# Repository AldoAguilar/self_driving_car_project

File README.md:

# Self Driving Car Project
This repository is dedicated to the development of a robotic system capable of performing an autonomous driving behavior of a 1/10 RC Vehicle using Control algorithms based in Deep Neural Networks through ROS.

## Table of Contents

* [Project Description](#project-description)
* [Installation](#installation)
  - [Hardware prerequisites](#hardware-prerequisites)
  - [Software prerequisites](#software-prerequisites)
  - [Hardware setup](#hardware-setup)
  - [Software setup](#software-setup)
  - [Network setup](#network-setup)
* [ROS Architecure](#ros-architecture)

## Project Description
The objective of this project is to develop an autonomous driving robotic system using a 1/10 RC Vehicle which is instrumented using specific hardware to control and measure its velocity and direction through ROS. As mentioned, a Deep Neural Network is used to Control the autonomous behavior of the vehicle which is trained and tested using the information of the vehicle's direction and speed data as well as visual and spatial information provided by an RGB/Depth camera and a Lidar sensor mounted in the vehicle.

## Installation
The following steps are aimed to help the user replicate the setting up of the project at its current state, as well as giving an overall understanding of the implemented system.

| NOTE: This tutorial serves as a guide to setup the project to run with the listed hardware and softwares specifications however it is recommended that any new contributor makes the effort of migrating the current state of the project to the newest software and hardware requisites as it will guarantee a longer support and the potential implementation of newer packages that might help push the project forward in the future.  |
| --- |

### Hardware Prerequisites
* [Turnigy Trooper SCT-X4 1/10 4x4 Nitro Course Truck](https://hobbyking.com/es_es/turnigy-trooper-sct-x4-1-10-4x4-nitro-short-course-truck-rtr.html) [[1](#references)]
* [7.4V 2S LiPo battery with XT60 Connector](https://hobbyking.com/es_es/turnigy-2200mah-2s-30c-lipo-pack.html?queryID=61017de534bd628a334581b6a7d83735&objectID=18290&indexName=hbk_live_magento_es_es_products)
* [Matek PDB-XT60 (Power Distribution Board)](https://articulo.mercadolibre.com.mx/MLM-612335416-placa-de-distribucion-poder-pdb-drone-ubec-12v-y-5v-drone-_JM?quantity=1) [[2](#references)]
* [XI4005 Step Down Voltage Regulator](https://articulo.mercadolibre.com.mx/MLM-714620453-modulo-step-down-regulador-xl4005-5-32v-a-125-32v-5a-75w-_JM)
* [6 pins ON/OFF Switch](https://articulo.mercadolibre.com.mx/MLM-677740634-switch-interruptor-balancin-con-piloto-on-off-6-patas-2p-2t-_JM?quantity=1#position=5&type=item&tracking_id=82bb2446-1a24-42d8-a4a6-f555bc81b157)
* [12 AWG Silicon Cable](https://articulo.mercadolibre.com.mx/MLM-705048819-cable-12-awg-silicon-suave-drone-2mt-rojo-negro-bateria-lipo-_JM?quantity=1)
* [16 AWG Silicon Cable](https://articulo.mercadolibre.com.mx/MLM-599509724-cable-16-awg-silicon-60cm-30cm-negro-30-rojo-dron-robotica-_JM)
* [XT60 2 Female 1 Male Parallel Adapter (Y Connector)](https://www.amazon.com.mx/gp/product/B07W99CWS9/ref=ppx_yo_dt_b_asin_title_o05_s00?ie=UTF8&psc=1)
* [HXT 4mm to XT60 Male Adapter](https://www.amazon.com/Pack-XT60-Male-Conversion-Adapters/dp/B072BQBH92)
* [XT60 Male and Female Connectors](https://www.amazon.com.mx/gp/product/B01CQ2ON6Q/ref=ppx_yo_dt_b_asin_title_o00_s00?ie=UTF8&psc=1)
* [5.5mm Jack Male Connector](https://articulo.mercadolibre.com.mx/MLM-698487860-conector-jack-de-voltaje-macho-o-hembra-cable-55mm-21mm-_JM?quantity=1&variation=40282986743#position=4&type=item&tracking_id=72f44a5c-2100-46d6-a7ed-027b24ecf050)
* [Turnigy 9X 9Ch Mode 2 Transmitter and Receiver](https://hobbyking.com/es_es/turnigy-9x-9ch-mode-2-transmitter-w-module-ia8-receiver-afhds-2a-system.html) [[3](#references)]
* [Turnigy RC ON/OFF Switch](https://hobbyking.com/es_es/turnigy-receiver-controlled-switch-1.html) [[4](#references)]
* [Rotative Incremental Encoder](https://articulo.mercadolibre.com.mx/MLM-711576184-encoder-rotativo-incremental-para-calcular-distancia-y-velocidad-_JM)
* [Anker USB 3.0 Hub 0.7ft](https://www.anker.com/es/products/variant/4port-usb-30-ultra-slim-data-hub/A7516011)
* [Startech 15cm USB A to Mini B Cable](https://www.amazon.com.mx/gp/product/B003WV5DME/ref=ppx_yo_dt_b_asin_title_o01_s00?ie=UTF8&th=1)
* [Startech 15cm USB A to Micro B Cable](https://www.amazon.com.mx/gp/product/B00NTR1D8E/ref=ppx_yo_dt_b_asin_title_o02_s00?ie=UTF8&psc=1)
* [Wi-Fi USB Adapter](https://www.steren.com.mx/adaptador-usb-wi-fi.html)
* [Odroid XU4](https://wiki.odroid.com/odroid-xu4/odroid-xu4) [[5](#references)]
* [Intel Realsense SR300 / BlasterX Senz3D camera](https://es.creative.com/p/web-cameras/blasterx-senz3d) [[6](#references)]
* [RPLidar Laser Range Scanner A2](https://www.slamtec.com/en/Lidar/A2) [[7](#references)]
* [Configurable Network Router with Internet Access](https://www.linksys.com/es/p/P-WRT54GL/#product-features) [[8](#references)]
* Ethernet Cable
* External PC
* [Direction and Spped Control PCB](pc/kicad)
* [Arduino Nano](https://store.arduino.cc/usa/arduino-nano)

### Software prerequisites
* Ubuntu MATE 18.04 Operating System installed in the Odroid XU4 Board, installation guide can be found [here](https://wiki.odroid.com/odroid-xu4/getting_started/os_installation_guide#tab__odroid-xu4).
* Ubuntu 18.04 Operating System installed in the External PC.
  - Download the ISO file from [this link](http://releases.ubuntu.com/bionic/) by selecting the `64-bit PC (AMD64) desktop image`.
  - Create a bootable USB image of the ISO file. That process is explained in these links for [Windows](https://tutorials.ubuntu.com/tutorial/tutorial-create-a-usb-stick-on-windows#0) and [MacOS](https://tutorials.ubuntu.com/tutorial/tutorial-create-a-usb-stick-on-macos#0).
  - Installation process for Ubuntu 18.04 Operating System ca be found in [this tutorial](https://ubuntu.com/tutorials/tutorial-install-ubuntu-desktop#1-overview). *( Although a virtual machine with Ubuntu can be used in the external PC, it is recommended that Ubuntu runs natively in both computers. A recommended alternative to using a VM is [installing Ubuntu in a disk partition and using dual boot](https://www.tecmint.com/install-ubuntu-alongside-with-windows-dual-boot/) )*.

### Hardware setup
#### Electric connections

Setting up the electric connections is pretty straightforward, if working with an already mounted car it is recommended to check for any short circuit or damaged cable before connecting the battery or turning on the system. Remember to measure the output voltage of  the regulators before connecting any of the controller boards, guaranteeing an output voltage of around **5.25V**, and always validate that the LiPo battery is charged and balanced before running the system.

| NOTE: For more information regarding the implemented PCB mounting or for further updates and modifications go [here](pc/kicad). |
| --- |

| NOTE: If mounting a new system, consider using the hardware mentioned in the [hardware prerequisites](#hardware-prerequisites) section, it will be necessary to solder different elements of the system such as the ON/OFF Switch XT60 Connectors, the PDB XT60 Connectors and the Voltage Regulators input and output cables as well as the required components for the montage of the PCB. |
| --- |

#### Hardware montage
The montage of the different hardware components requires to manufacture certain elements such as two acrylic plates and a pair of support posts. This will function as the base for the hardware montage where each component is screwed with a corresponding spacer.

| NOTE: For more information regarding the implemented hardware montage or for further updates and modifications go [here](pc/freecad). |
| --- |

### Software setup
#### ODROID XU4

* Username: odroid
* Password: odroid

##### Clone GitHub repository
In a terminal, run the next command in your Home directory:
```
git clone http://github.com/AldoAguilar/self_driving_car_project
```
Add the project `setup.bash` file to your bash session so that it is sourced every time a new shell is launched:
```
echo "source ~/self_driving_car_project/odroid/catkin_ws/devel/setup.bash" >> ~/.bashrc
source ~/.bashrc
```

##### Configure Auto-Login
Run the following commands in terminal:
```
sudo su
cd /usr/share/lightdm/lightdm.conf.d
touch 60-lightdm-gtk-greeter.Configurenano 60-lightdm-gtk-greeter.conf
```
If the file isn't blank, add these to the end of the file. If the file is blank, add these lines to the file:

```
[SeatDefaults]
greeter-session=lightdm-gtk-greeter
autologin-user=odroid
```
Files in this directory are processed in alphabetical order.

The next time you reboot, the user specified after `autologin-user=` should be logged in automatically.
##### Installing ROS
Once Ubuntu MATE 18.04 has been installed in the board, it's necessary to install the ROS Melodic distribution. This section is based on the more in-depth tutorial from the ROS Wiki: [Ubuntu install of ROS Melodic](http://wiki.ros.org/melodic/Installation/Ubuntu). For a more detailed explanation please read the provided link.  

Setup your computer to accept software from packages.ros.org.

```
sudo sh -c 'echo "deb http://packages.ros.org/ros/ubuntu $(lsb_release -sc) main" > /etc/apt/sources.list.d/ros-latest.list'
```

Setup the keys:

```
sudo apt-key adv --keyserver 'hkp://keyserver.ubuntu.com:80' --recv-key C1CF6E31E6BADE8868B172B4F42ED6FBAB17C654
```

Make sure your package index is up-to-date:

```
sudo apt-get update
```

Perform a ROS Melodic full installation:
```
sudo apt-get install ros-melodic-desktop-full
```

Initialize rosdep:
```
sudo rosdep init
rosdep update
```
Setup your ROS environment variables to be automatically added to your bash session every time a new shell is launched:
```
echo "source /opt/ros/melodic/setup.bash" >> ~/.bashrc
source ~/.bashrc
```
Install other dependencies for building ROS packages:
```
sudo apt install python-rosinstall python-rosinstall-generator python-wstool build-essential
```

##### Arduino CLI Configuration
Go to the Odroid's Arduino Src Directory in `~/self_driving_car_project/odroid/src/arduino`.
It will be necessary to update the local cache of available platforms and libraries of the [arduino-cli](https://github.com/arduino/arduino-cli) tool, run the next command in terminal:

```
./arduino-cli core update-index
```

Install the core for Arduino Nano boards, run the next command in terminal:
```
./arduino-cli core install arduino:avr
```

#### JETSON NANO

The Jetson Nano will be responsible of managing the video, data management and Machine Learning algorithms. It wil be then necessary to install the required resources.

##### Clone GitHub repository
In a terminal, run the next command in your Home directory:
```
git clone http://github.com/AldoAguilar/self_driving_car_project
```

##### Install RealSense
The project depends on the utilization of the Intel Realsense Depth Camera SR300 which requires to install the Intel Realsense Libraries and drivers. The installation process can be different depending on the platform where the device is going to be used, however for total compatibility and support of this device it's recommended to make a native installation by compiling the resource code of the mentioned drivers.

The Jetson Nano as well as many other development platforms comes with a predefined Kernel with support for specific type of devices however it's possible to allow different devices by recompiling the boards kernel and enabling the required resources to allow the support for the mentioned devices. The Intel Realsense Cameras require specific Kernel patches for it to be natively compiled. For more information you can visit [this](https://github.com/JetsonHacksNano/installLibrealsense/tree/vL4T32.2.1) GitHub repository used as a basis for the installation scripts defined in this project.

To path the Jetson Nano's kernel for Intel Realsense Cameras support, go to the `realsense` directory and execute the command:
```
sudo ./pathcKernel.sh
```
This script will automatically install all the required resources for the kernel patch and recompile the loaded kernel, it's a long process that may take several minutes. Once it has concluded you will have to reboot your board in order to proceed with the Librealsense Libraries and Drivers.

Once the Kernel patch has been successfully achieved, return to the `realsense`directory and execute the next command:

```
sudo ./installLibrealsense.sh
```

This will install all the required resources and compile the Intel Librealsense libraries for its usage in your Jetson Nano board. It's a long process that may take several minutes to be completed. Finally you can run the command `rs-depth` in terminal with the SR300 Camera connected to see a Plain Text representation of the depth values obtained vy the camera, validating the correct installation of the resources.

##### Install ROS
Go to the Jetson Install Resources Directory in `~/self_driving_car_project/jetson/install`, the go to the `ros` directory and run the command:
```
sudo ./installROS.sh
```
This will execute a Shell Script that will automatically install all ROS Melodic Resources for the Jetson Nano.
It's important to run this script after having installed the Intel Realsense resources as it will also install the Realsense ROS Package that requires the Librealsense Libraries and Drivers to be installed first.

##### Install Tensorflow
As mentioned, the Jetson Nano will be used to execute all the Machine Learning processes, Tensorflow will be the selected platform to achieve this purpose, in order to install this Platform, go to the `tensorflow` install epository and execute the command:

```
sudo ./installTensorFlow.sh
sudo ./installKeras.sh
```
This will install the Tensorflow and Keras resources in your board.

### Network setup

The project is conformed of three network devices working together the Jetson Nano and Odroid Development boards and the Personal PC used to monitor the execution of the project at a given moment. To achieve this communication, it's necessary to have a reserved router used to manage all network traffic between this devices. In this project the selected router is the [Linksys Wireless-G WRT54GL](doc/datasheets/WRT54GL_Manual.pdf),  

*NOTE: Notice that the IP Addresses displayed in the previous image are not necessarily consistent with the ones used in the project.*

As already mentioned, the project will mainly run over ROS, therefore it's necessary to take into consideration the [ROS Network Architecture](http://wiki.ros.org/ROS/NetworkSetup). However you'll surely have some considerations to take into account. Mainly as specified in the network configuration, your personal PC and the Odroid Board will be directly connected to the Router, the PC will be connected via ethernet, while the Odroid Board will be connected using the USB WiFi Adapter. The Jetson board is connected to the Odroid board with an ethernet cable, however it's easy to observe that this connection correspond to a specific LAN formed by the Odroid and the Jetson's ethernet connection only and do not correspond to the same network that your PC and the Odroid Wireless adapter are part of. This can be concluded by observing the assigned IP Addresses of the previously displayed Architecture.

ROS Network Setup requires a full connectivity between all the devices, in this case the PC, Odroid and Jetson board. However this cannot be directly achieved if, as previously stated, the Jetson and Odroid boards conform a different Network than the one between the PC and the Odroid board, but this doesn't mean that the connectivity between for instance between your PC and the Jetson board cannot be achieved. In general the connectivity between different networks can be achieved by using routing tables and allowing the Odroid board to share the router connectivity to the Jetson board through its ethernet adapter connection.

The general network setup to be achieved can be described in steps:
1. Connect your Router to a Internet enabled connection via ethernet (i.e. One of your modem Ethernet ports).
2. Connect your PC to the router either using your PC Wireless or ethernet adapter.
3. Connect your Odroid board to the router using the USB WiFi adapter.
4. Look for the IP Addresses of both your PC and the Odroid board WiFi adapter.
5. In your PC, ping your Odroid board i.e:
```
ping 192.168.1.1
```
6. In your Odroid ping your PC i.e:
```
ping 192.168.1.3
```
7. If internet connection is desired in your devices, enter any browser and try to open any URL (i.e: https://github.com/AldoAguilar/self_driving_car_project).
8. Enable shared wireless connection in your Odroid in order to share the stablished wireless connection with your Jetson board, you can follow the instructions given in [this post](https://askubuntu.com/questions/359856/share-wireless-internet-connection-through-ethernet) .
9. Look for the IP Addresses of both your Odroid and Jetson ethernet adapters.
10. In your Odroid board, ping the Jetson board ethernet adapter i.e:
```
ping 10.47.0.2
```
11. In your Jetson board, ping the Odroid board ethernet adapter i.e:
```
ping 10.47.0.1
```
12. If the pings succeeded you are ready to establish the routing table and firewall configurations in order to achieve the desired full connectivity. We'll start with the firewall configuration, it's easy to acknowledge that the device responsible of translating a message from one network to the other is the Odroid board as it's the only device that is connected to both LANs.    
A firewall can block or allow the traffic of network messages from different IP addresses/networks to another. By default the firewall configuration of this board can be problematic as at some point it can cause the blocking of network messages whether coming from the Personal PC or the Jetson board.  
Although this firewall configurations can be managed depending on the actual architecture of your network this guide will recommend to disable the firewall in your Odroid board so that any traffic from any network can be accepted by the board and redirected to any network adapter. *NOTE: Disabling the firewall can cause certain security issues in your device, it's highly recommended that the firewall is disabled only if your device has no connection the internet and is only working in a managed LAN network.*  
In order to disable the Odroid's firewall configuration open a terminal window and type the next command:
```
sudo iptables -F
```
13. Finally it'll be necessary to define the routing tables so that the complete connectivity can be achieved. The main procedure can be read in [this post](https://answers.ros.org/question/256070/problems-with-communication-between-multiple-machines/). For instance, in the case of the displayed network sample, in your personal PC introduce the command:
```
sudo route add -net 10.47.0.0 netmask 255.255.255.0 gw 192.168.1.1
```
This command states that any device in the _10.47.0.0/24_ network can be found uding the connection with the device with IP _192.168.1.2_ which corresponds to the Odroid's WiFi adapter.  
In the case of the Jetson's routing table, in your Jetson board introduce the command:
```
sudo route add -net 192.168.1.0 netmask 255.255.255.0 gw 10.47.0.1
```

## ROS Architecture

## References
1. Turnigy. (2016). *Trooper SCT-X4 User Manual*. Retrieved from: [https://hobbyking.com/es_es/turnigy-trooper-sct-x4-1-10-4x4-nitro-short-course-truck-rtr.html](doc/datasheets/SCT-X4_Manual.pdf)
2. Matek. (2020). *PDB-XT60 User Manual*. Retrieved from: [http://www.mateksys.com/?portfolio=pdb-xt60#tab-id-3](doc/datasheets/PDB-XT60_Manual.pdf)
3. Turnigy. (2016). *Turnigy 9x 2.4GHz radio TGY User Manual*. Retrieved from: [https://hobbyking.com/media/file/725056143X2037269X20.pdf](doc/datasheets/TGY-9x-9CH_Manual.pdf)
4. Turnigy. (2016). *Turnigy R/C Electronic Switch Manual*. Retrieved from: [https://cdn-global-hk.hobbyking.com/media/file/t/u/turnigy_rc_switch_manual.pdf](doc/datasheets/RC-Switch_Manual.pdf)
5. Odroid XU4. (2017). *Odroid XU4 User Manual*. Retrieved from: [https://magazine.odroid.com/wp-content/uploads/odroid-xu4-user-manual.pdf](doc/datasheets/Odroid-XU4_Manual.pdf)
6. Intel Corporation. (2016). *Intel RealSense Camera SR300*. Retrieved from: [https://www.mouser.com/pdfdocs/intel_realsense_camera_sr300.pdf](datasheets/RealSenseCamera-SR300_Manual.pdf)
7. Slamtec. (2016). *RPLidar A2 User Manual*. Retrieved from: [https://www.generationrobots.com/media/robopeak_2d_lidar_brief_en_A2M4.pdf](doc/datasheets/RPLidar-A2_Manual.pdf)
8. Linksys. (2016). *Linksys Wireless-G WRT54GL Manual*. Retrieved from: [https://downloads.linksys.com/downloads/userguide/1224639055327/WRT54Gv7-EU_UG.pdf](doc/datasheets/WRT54GL_Manual.pdf)

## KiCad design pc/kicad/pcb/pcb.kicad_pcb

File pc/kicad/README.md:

# Self Driving Car Project KiCad PCB Design
This directory includes the [KiCad](https://www.kicad-pcb.org/) **"pcb"** project, used to design the Direction and Speed Controller PCB implemented in the Self Driving Car Project.   

| NOTE: The KiCad EDA Suite was used for the development of this project based on its Open Source and Cross Platform Characteristics, allowing any user to have access and modify the provided resources for future updates or modifications. For more information on the KiCad EDA Suite go [here](https://www.kicad-pcb.org/).  |
| --- |

## Table of Contents

* [Project Description](#project-description)
* [Installation](#installation)
  - [Software prerequisites](#software-prerequisites)
  - [Hardware prerequisites](#hardware-prerequisites)
  - [Software setup](#software-setup)
  - [Hardware setup](#hardware-setup)

## Project Description
The objective of this project is to develop the Self Driving Car Direction and Speed Controller PCB, it includes the required sources to develop and modify this board using the Open Source KiCad EDA Software, including a general description of this project and the required prerequisites for its implementation.

## Installation
The following steps are aimed to help the user replicate the setting up of the project at its current state, as well as giving an overall understanding of the implemented system.

| NOTE: This tutorial serves as a guide to setup the project to run with the listed hardware and softwares specifications however it is recommended that any new contributor makes the effort of migrating the current state of the project to the newest software and hardware requisites as it will guarantee a longer support and the potential implementation of newer packages that might help push the project forward in the future.  |
| --- |

### Software Prerequisites
In order to open and make use of the **"pcb"** source files it'll be necessary to install the KiCad EDA Suite in your computer:
* Go to the [KiCad EDA Download section](https://www.kicad-pcb.org/download/) and select your Operating System.
* Follow the installation instructions for KiCad's Stable Release.
* Search for the KiCad Application in your PC and open it.
* You'll se a window similar to:

* Go to the [pcb project directory](pcb) and open the **pcb.pro** file.
* You'll now see a tree view in the left menu box similar to:

### Hardware Prerequisites
* [Arduino Nano](https://store.arduino.cc/usa/arduino-nano)
* [Dual Terminal Block](https://articulo.mercadolibre.com.mx/MLM-606057911-borneras-bornes-terminales-conexion-pcb-arduino-robotica-_JM?matt_tool=65873753&matt_word&gclid=Cj0KCQjwy6T1BRDXARIsAIqCTXpDgjaNT2CEy81dMAPUocUoDs2DkgAVtDDbl-tf0lpIVRkcGjDF6mAaAjMkEALw_wcB&quantity=1)
* [16 Pin IC Socket](https://articulo.mercadolibre.com.mx/MLM-747897431-base-socket-para-circuito-integrado-16-pines-pack-20-piezas-_JM?quantity=1#position=6&type=item&tracking_id=53bed74d-7c0d-4ee6-b2de-27034858cc5a)
* [74LS157 IC](https://articulo.mercadolibre.com.mx/MLM-719086073-10pzs-74ls157-74157-multiplexor-y-selector-de-datos-_JM?quantity=1#position=1&type=item&tracking_id=8baa4de1-5f68-43eb-a4a4-0d66c8946778)
* [Female Header Connectors](https://articulo.mercadolibre.com.mx/MLM-686462836-header-hembra-cuadrada-40-pines-254mm-mv-electronica-_JM?quantity=1#position=4&type=item&tracking_id=ec4faa2c-5fe0-4fe5-9e25-1ca4e9676792)
* [Male Header Connectors](https://articulo.mercadolibre.com.mx/MLM-686756465-header-macho-40-pines-254mm-1-pz-arduino-mv-electronica-_JM?quantity=1#reco_item_pos=1&reco_backend=machinalis-seller-items-pdp&reco_backend_type=low_level&reco_client=vip-seller_items-above&reco_id=c50f5536-5ffa-46cc-8689-cafcea0cb692)

### Software Setup
The **"pcb"** KiCad Project includes different source files required for the creation of the Self Driving Car Project Direction and Speed Controller PCB. The project is mainly conformed of four main design files: **pcb.sch**, **pcb.lib**, **pcb.net**, **pcb.kicad_pcb**.  _(Follow the instructions included in the [Installation](#installation) section in order to open the pcb project, here you will find the mentioned design files)_.

The **pcb.sch** file includes the PCB Schematic Sheet, in here you can find the electric connections and the components and conform the design. In general, the design is conformed of eleven Jumper Connectors, a 74LS157 IC and two Arduino Nano, where:

* **J1 to J6**: Correspond to the Radio Control Receiver Connectors which will handle the received Speed, Direction an Operation Mode Control Signals from the Radio Control Transmitter.
* **J7**: Corresponds to the RC ON/OFF Switch three line connector which will receive the Radio Control Operation Mode Signal.
* **J8**: Corresponds to the Car's Speed Motor three line connector which will receive the generated Speed Control Signal.
* **J9**: Corresponds to the Car's Directional Servo Motor three line connector which will receive the generated Direction Control Signal.
* **J10**: Corresponds to the Car's Speed Encoder four line connector which will receive the Encoder Output Signal.
* **J11**: Corresponds to the RC ON/OFF Switch two line output Terminal Connector.
* **74LS157**: Dual Multiplexer used to select the desired Direction and Speed Control signals, it receives the Radio Control and Arduino generated Control signals and used the received Operation Mode Control Signal (RC ON/OFF Switch Output) to select between the mentioned outputs.
* **Arduino Nano 1**: Generates the desired autonomous Direction and Speed Control Signals, it receives the desired Speed and Direction values via USB Connection with the Odroid Board. _(For more information regarding the Arduino Nano 1 functionality go [here](../../odroid/src))_.
* **Arduino Nano 2**: Gets the generated Direction and Speed Control Signals as well as the Encoder Output and transmits this information via USB Connection with the Odroid Board. _(For more information regarding the Arduino Nano 2 functionality go [here](../../odroid/src))_.

The **pcb.lib** file includes the Footprint library used by the project to assigned the desired Footprints to the used components in the Schematic Sheet.

The **pcb.net** file includes the Schematic mapping with the required PCB Footprints, allowing to assign a specific Footprint to each of the components added to the PCB Schematic Sheet.

The **pcb.kicad_pcb** includes the final PCB design, including the Component Footprints, Connections, etc. Here, you can find the representation for he Schematic Components with the assigned Footprints as assigned in the .net file.

### Hardware Setup
The hardware setup is really straightforward, in general it will be necessary to follow the PCB footprints and Labels. In particular the main consideration to be taken is that any header connector is marked with a **dot** that specifies the GND connector, which means that any cable that must be connected to these headers require to have its GND pin attached to de **dot** marked pin of the connector. Also look for the orientation of the Multiplexor IC which can be identified by its footprint, and in the case of the Arduino Nano, the orientation can be determined by the USB Label marking the side where the USB Mini B connector must be placed.

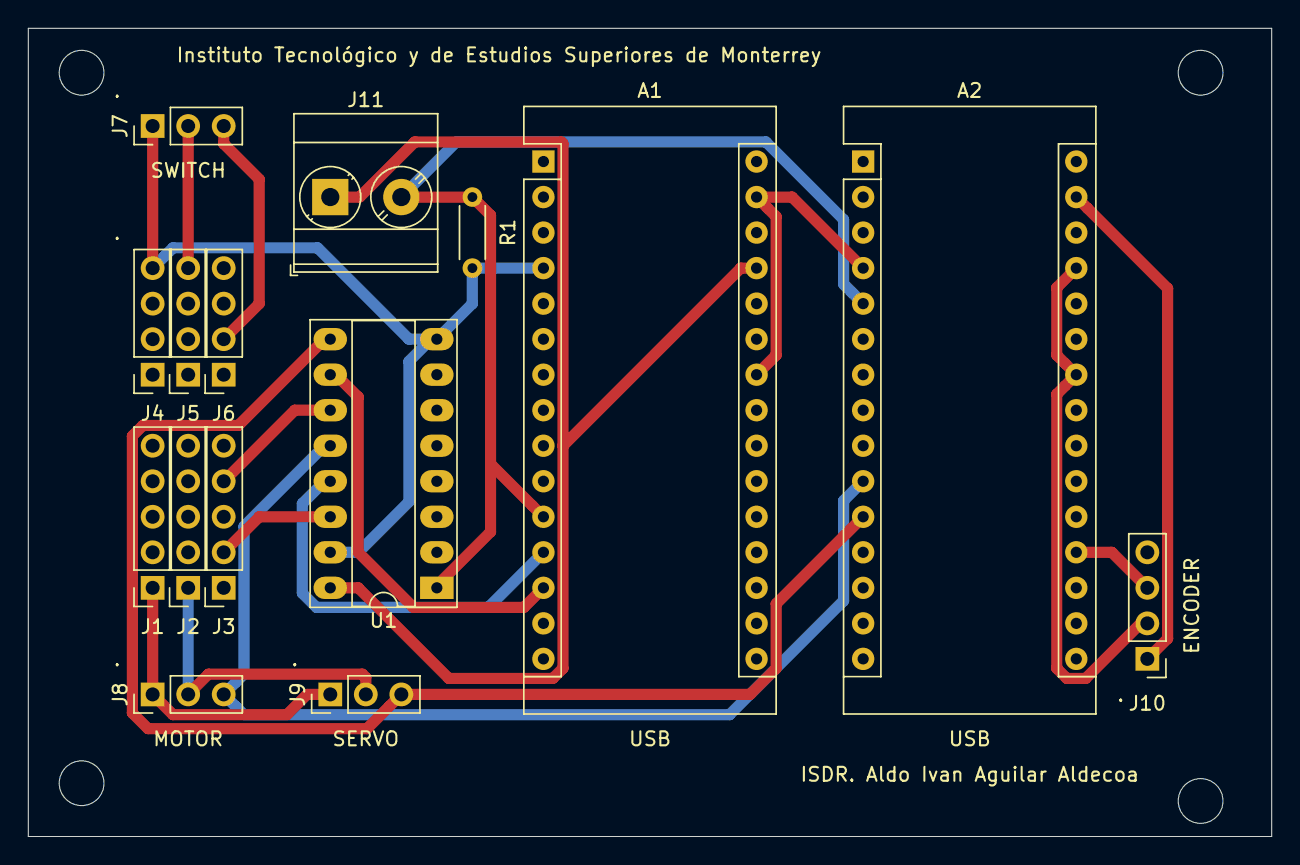
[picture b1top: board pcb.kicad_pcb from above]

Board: 2 copper layers, 88.9 x 57.8 mm, 15 parts (0 on the bottom side), 13 nets.

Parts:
A1, A2: Arduino_Nano_v3.x; Arduino_Nano
J1, J2, J3: Conn_01x05; PinSocket_1x05_P2.54mm_Vertical
J4, J5, J6: Conn_01x04; PinSocket_1x04_P2.54mm_Vertical
J7, J8, J9: Conn_01x03; PinHeader_1x03_P2.54mm_Vertical
J10: Conn_01x04; PinHeader_1x04_P2.54mm_Vertical
J11: Conn_01x02; TerminalBlock_Phoenix_MKDS-3-2-5.08_1x02_P5.08mm_Horizontal
R1: 4.7k; R_Axial_DIN0204_L3.6mm_D1.6mm_P5.08mm_Horizontal
U1: 74LS157; DIP-16_W7.62mm_Socket_LongPads

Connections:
/5V1: A1.27, J11.1, U1.16
/5V2: A2.24, A2.27, J10.2
/ENCODER: A2.19, J10.3
/GND: A1.4, A1.24, A1.29, A2.4, A2.29, J1.1, J4.4, J7.1, J8.1, J9.1, J10.1, R1.2, U1.8, U1.15
/INTERRUPT: A1.11, A2.5, J11.2, R1.1, U1.1
/MOTOR_ARD: A1.12, U1.13
/MOTOR_OUT: A2.10, J8.3, U1.12
/MOTOR_RF: J3.2, U1.14
/SERVO_ARD: A1.13, U1.10
/SERVO_OUT: A2.11, J9.3, U1.9
/SERVO_RF: J3.4, U1.11
/SWITCH_RF: J6.2, J7.3
/VDD: J2.1, J5.4, J7.2, J8.2, J9.2

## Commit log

2020-05-20 Repository Initialization
2020-05-21 CAD Large Plate Modifications
2020-05-21 Large Plate CAD Modifications
2020-06-08 Readme actualization
2020-06-11 README updates and FreeCAD Designs added
2020-06-11 Directory modifications
2020-06-11 README modifications
2020-06-12 Encoder file added.
2020-07-08 SensorsCode and Wheel Mounts CAD Modified.
2020-07-20 General additions to Actuators and Sensors Scripts
2020-11-17 General Modifications
